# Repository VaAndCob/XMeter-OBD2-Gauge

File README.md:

# X-Meter: A DIY OBD2 Multi-Gauge and Diagnostic Tool (c. 2007)

## Introduction

This repository contains the complete project files for the X-Meter, a custom-built hardware device for automotive diagnostics and real-time data display. This legacy project was developed around 2007 as a passion project for the car enthusiast community.

The X-Meter connects to a vehicle's OBD2 port and provides a wealth of information, acting as a multi-gauge, trip computer, and diagnostic scanner.

## Core Technology

*   **Microcontroller:** The hardware is powered by an 8051-family microcontroller.
*   **OBD2 Interface:** It uses an ELM327-compatible chip for vehicle communication.
*   **Firmware:** The firmware is written in Assembly language.
*   **PC Software:** The updater and configuration utility were programmed in Delphi 7.

## Features

*   **Real-time Data Display:** Shows two selectable engine parameters simultaneously (e.g., RPM, vehicle speed, coolant temp, engine load, etc.).
*   **Diagnostic Tool:** Can read and clear Diagnostic Trouble Codes (DTCs) and reset the Powertrain Control Module (PCM).
*   **Customizable Alerts:** Set visual and audible warnings for user-defined limits (e.g., high coolant temperature).
*   **Configurable Interface:** Adjust backlight, sound, and auto-sleep settings.
*   **Expandable:** The hardware design includes an extension port for future functionality.

## Gallery

| Front View | Rear View |
|:---:|:---:|
|  |  |

| Updater Software | Warning Limit Feature |
|:---:|:---:|
|  |  |

## Project Structure

*   `Hardware/`: Contains hardware design files (schematics, PCB layouts for v1 and v2) and hardware images.
*   `Webpage/`: The original HTML webpage and images used to document the project.
*   `XFirmware/`: The 8051 assembly source code (`.asm`) and compiled firmware (`.hex`).
*   `Hex2Const/`: A Delphi 7 project for the PC-based firmware updater and configuration utility.
*   `XUpdater/`: Files related to the firmware updater tool.
*   `XMETER_prototype/`: (Outdated) Files from the early prototyping stage.

## Disclaimer

This is a legacy project from 2007. The files are provided as-is for historical and educational purposes. Some of the tools, libraries, and links in the original documentation may be outdated.

## Credits

This project was designed and developed by Va&Cob(**Jerry**)

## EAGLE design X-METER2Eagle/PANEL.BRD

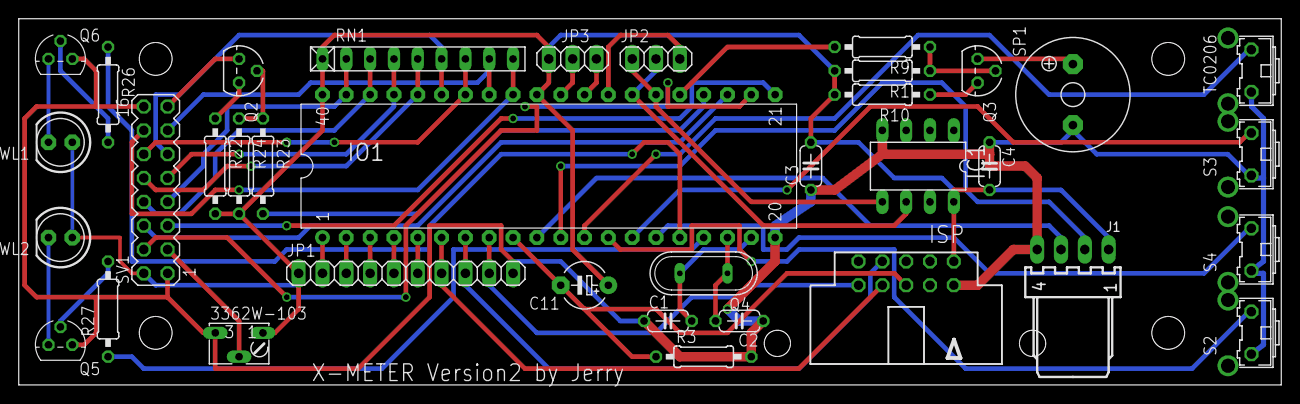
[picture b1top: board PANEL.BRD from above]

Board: 2 copper layers, 134.6 x 39.0 mm, 36 parts (0 on the bottom side), 50 nets.

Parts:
3362W-103: 10K; B64W
C1, C2: 30pF; C050-024X044
C3, C4: 0.1uF; C050-024X044
C11: 10uF/16v; E5-5
IC1: 24LC01; DIL8
IO1: AT89S8253-24; PDIP40
ISP: ISP; 057-010-0
J1: DLC; 7395-04
JP1: EXT; 1X10
JP2: JP2; 1X03
JP3: JP3; 1X03
Q2, Q3: BC557; TO92
Q4: 22.118MHz; QS
Q5, Q6: BC547; TO92
R1, R3, R24, R26, R27: 10K; 0207/10
R9, R23: 1K; 0207/10
R10, R22: 10R; 0207/10
RN1: 10K; RN-9
S2: BL; B3F-31XX
S3: UP; B3F-31XX
S4: DN; B3F-31XX
SP1: HCM1206X; KSS1201
SV1: LCD; MA08-2
TC0206: MENU; B3F-31XX
WL1, WL2: LED5MM

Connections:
GND: 3362W-103.E, C1.1, C2.1, C3.1, C4.1, IC1.4, IO1.20, ISP.2, J1.4, JP1.10, Q5.1, Q6.1, R3.2, S2.1, S3.1, S4.1, SP1.-, SV1.1, SV1.16, TC0206.1
unnamed: IO1.14, S3.2
unnamed: Q2.3, SV1.15
unnamed: IO1.15, S4.2
unnamed: IO1.11, J1.2
unnamed: IC1.5, IO1.26, JP2.1
unnamed: IC1.6, IO1.27, JP2.2
unnamed: IO1.38, RN1.3, SV1.8
unnamed: C11.-, IO1.9, ISP.6, R3.1
unnamed: IO1.37, RN1.4, SV1.9
unnamed: IO1.36, RN1.5, SV1.10
unnamed: IO1.35, RN1.6, SV1.11
unnamed: IO1.34, RN1.7, SV1.12
unnamed: IO1.33, RN1.8, SV1.13
unnamed: IO1.32, RN1.9, SV1.14
unnamed: Q2.1, R22.1
unnamed: IO1.23, SV1.6
unnamed: 3362W-103.S, SV1.3
unnamed: IO1.13, S2.2
unnamed: C1.2, IO1.19, Q4.2
unnamed: IO1.10, J1.3
unnamed: IO1.12, TC0206.2
unnamed: IO1.8, ISP.10, JP1.9
unnamed: Q3.3, SP1.+
unnamed: IO1.28, JP2.3
unnamed: IO1.6, ISP.8, JP1.7
unnamed: Q2.2, R23.1, R24.1
unnamed: Q3.2, R1.1, R9.1
unnamed: Q3.1, R10.1
unnamed: IO1.39, RN1.2, SV1.7
unnamed: IO1.7, ISP.7, JP1.8
unnamed: IO1.25, R9.2
unnamed: IO1.22, SV1.4
unnamed: IO1.21, SV1.5
unnamed: IO1.24, R23.2
unnamed: Q6.3, WL1.K
unnamed: C2.2, IO1.18, Q4.1
unnamed: Q6.2, R26.2
unnamed: Q5.2, R27.2
unnamed: IO1.16, R26.1
unnamed: IO1.17, R27.1
unnamed: IO1.5, JP1.6
unnamed: IO1.3, JP1.4
unnamed: IO1.4, JP1.5
unnamed: IO1.2, JP1.3
unnamed: IO1.1, JP1.2
unnamed: IO1.30, JP3.2
unnamed: IO1.29, JP3.3
VCC: 3362W-103.A, C3.2, C4.2, C11.+, IC1.8, IO1.31, IO1.40, ISP.1, J1.1, JP1.1, JP3.1, R1.2, R10.2, R22.2, R24.2, RN1.1, SV1.2, WL1.A, WL2.A
WL2: Q5.3, WL2.K

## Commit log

2025-08-24 remove duplicated files
2025-08-24 add gitignore
2025-08-24 readme update
2025-08-24 files added
2025-09-08 rename files
